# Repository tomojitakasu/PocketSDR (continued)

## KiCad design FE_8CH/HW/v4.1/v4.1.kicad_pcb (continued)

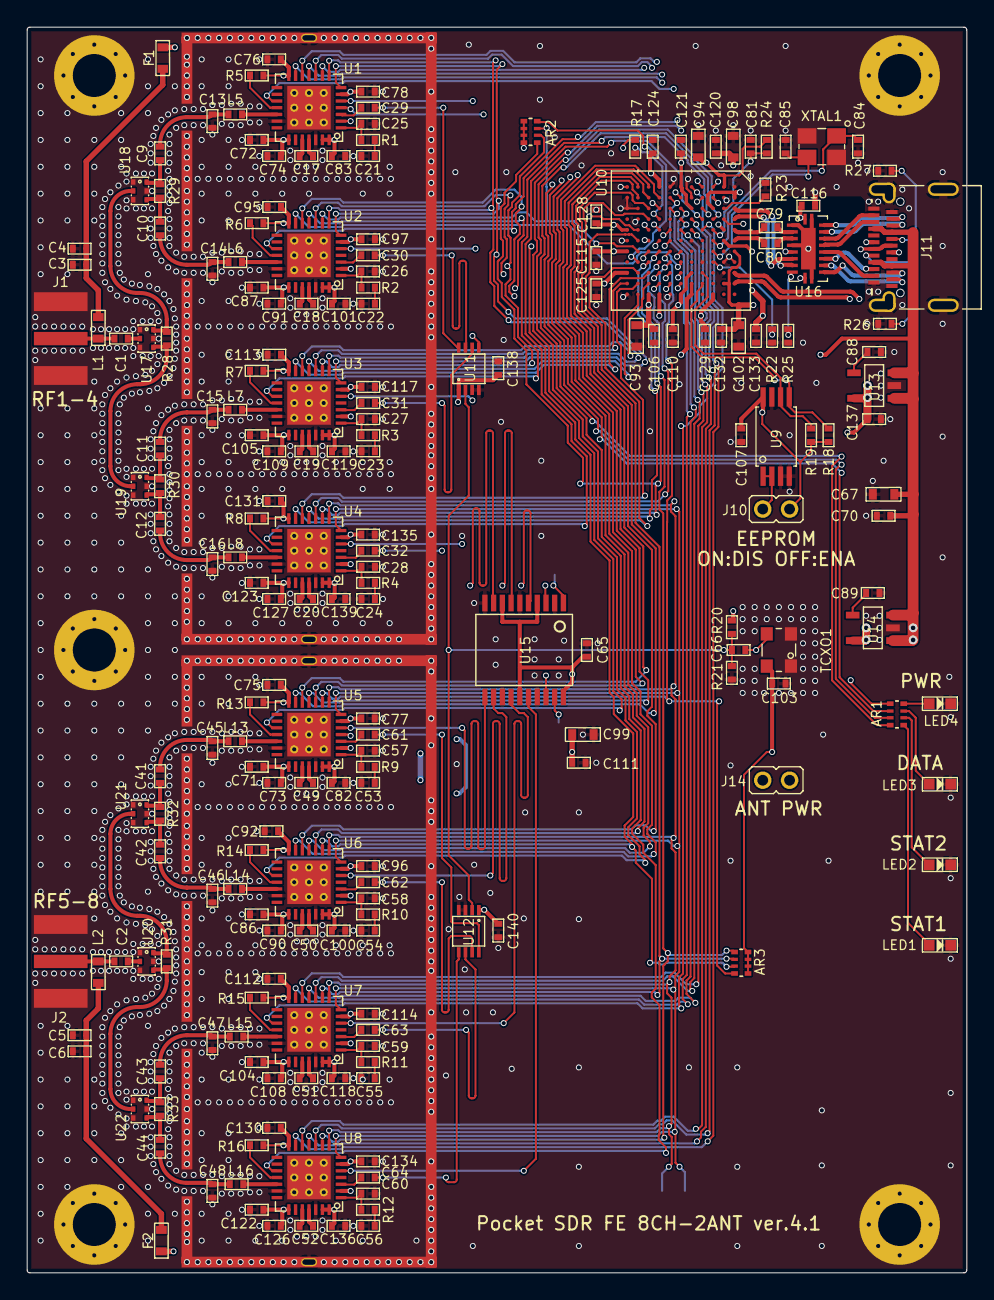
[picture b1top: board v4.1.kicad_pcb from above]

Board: 4 copper layers, 70.0 x 92.8 mm, 221 parts (0 on the bottom side), 195 nets.

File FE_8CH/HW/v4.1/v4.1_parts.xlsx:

No | Reference | Value | Package | Qty | Assy | Supplier | Supplier Part # | Digikey Part # | Price | Total | URL
1 | U1-U8 | RF RX GNSS 1.227/1.575GHZ | TQFN28 | 8 | 8 | Maxim | MAX2771ETI+ | MAX2771ETI+-ND | 1883 | 15064 | https://www.digikey.jp/products/ja?keywords=MAX2771ETI%2B-ND
2 | U9 | I2C EEPROM 1MBIT | 8-TSSOP | 1 | 1 | Microchip | AT24CM01-XHM-T | AT24CM01-XHM-TCT-ND | 284 | 284 | https://www.digikey.jp/ja/products/detail/microchip-technolo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
3 | U10 | EZ-USB FX3 USB 3.0 RAM 512KB | 121-TFBGA | 1 | 1 | Cypress | CYUSB3014-BZXC | 448-CYUSB3014-BZXC-ND | 5308 | 5308 | https://www.digikey.jp/ja/products/detail/infineon-technolog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
4 | U11, U12 | IC CLK BUFFER 1:4 | 8-VSSOP | 2 | 2 | Nexperia | 74AVC9112DCH | 1727-7845-1-ND | 91 | 182 | https://www.digikey.jp/ja/products/detail/nexperia-usa-inc/7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
5 | U13 | LDO 1.2V 500mA | SOT23-5 | 1 | 1 | MaxLinear | SPX3819M5-L-1-2/TR | 1016-1872-1-ND | 88 | 88 | https://www.digikey.jp/ja/products/detail/maxlinear-inc/SPX3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
6 | U14 | LDO 3.3V 500mA | SOT23-5 | 1 | 1 | MaxLinear | SPX3819M5-L-3-3/TR | 1016-1873-1-ND | 88 | 88 | https://www.digikey.jp/ja/products/detail/maxlinear-inc/SPX3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
7 | U15 | IC CLK BUFFER 1:10 100MHZ | 20SSOP | 1 | 1 | Renesas | 74FCT3807APYG | 800-1628-5-ND | 295 | 295 | https://www.digikey.jp/ja/products/detail/renesas-electronic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
8 | U16 | IC MUX/DEMUX USB 3.0 | 20TQFN | 1 | 1 | Diodes | PI3USB302-AZBEX | PI3USB302-AZBEXCT-ND | 419 | 419 | https://www.digikey.jp/ja/products/detail/diodes-incorporate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
9 | U17-U22 | RF PWR DVDR 950MHZ-2.15GHZ | 2.04 x 1.29 SMD | 6 | 6 | TTM | PD0922J5050S2HF | 1173-1094-1-ND | 160 | 960 | https://www.digikey.jp/product-detail/ja/anaren/PD0922J5050S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
10 | TCXO1 | TCXO 24.000 MHz 0.5ppm Clipped-sine | 2.5 x 2 SMD | 1 | 1 | Epson | TG2520SMN 24.0000M-MCGNNM3 | - | 567.6 | 567.6 | https://www.mouser.jp/ProductDetail/Epson-Timing/TG2520SMN-2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
11 | XTAL1 | XTAL 19.2MHz | 2.5 x 2 SMD | 1 | 1 | NDK | CS05400-19.2M | 644-CS05400-19.2MCT-ND | 132 | 132 | https://www.digikey.jp/ja/products/detail/ndk-america-inc/CS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
12 | C3, C5, C71, C72, C86, C87, C104, C105, C122, C123 | 100pF | C1005 | 10 | 10 | Kyocera | KGM05ACG1H101JH | 478-KGM05ACG1H101JHCT-ND | 3.8 | 38 | https://www.digikey.jp/ja/products/detail/kyocera-avx/KGM05A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
13 | C4, C6, C65, C70, C73-C80, C82, C83, C88-C92, C95-C97, C100, C101, C103, C106-C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 | 0.1uF | C1005 | 58 | 58 | Kyocera | KGM05AR71C104KH | 478-KGM05AR71C104KHCT-ND | 2.5 | 145 | https://www.digikey.jp/ja/products/detail/kyocera-avx/KGM05A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
14 | C1, C2, C9-C12, C17-C20, C41-C44, C49-C52 | 470pF | C1005 | 18 | 18 | Kyocera | KGM05AR71H471KH | 478-KGM05AR71H471KHCT-ND | 3 | 54 | https://www.digikey.jp/ja/products/detail/kyocera-avx/KGM05A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
15 | C13-C16, C45-C48 | 1.7pF | C1005 | 8 | 8 | Murata | GJM1555C1H1R7BB01D | 490-6074-1-ND | 8.9 | 71.2 | https://www.digikey.jp/ja/products/detail/murata-electronics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
16 | C21-C24, C53-C56 | 750pF | C1005 | 8 | 8 | Taiyo Yuden | UMK105CH751JVHF | 587-5098-1-ND | 8 | 64 | https://www.digikey.jp/ja/products/detail/taiyo-yuden/UMK105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
17 | C25-C28, C57-C60 | 15pF | C1005 | 8 | 8 | Kyocera | KGM05ACG1H150JH | 478-KGM05ACG1H150JHCT-ND | 3.3 | 26.4 | https://www.digikey.jp/ja/products/detail/kyocera-avx/KGM05A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
18 | C29-C32, C61-C64, C66 | 0.01uF | C1005 | 9 | 9 | Kyocera | KGM05AR71C103KH | 478-KGM05AR71C103KHCT-ND | 2.4 | 21.599999999999998 | https://www.digikey.jp/ja/products/detail/kyocera-avx/KGM05A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
19 | C67, C93, C94, C98, C99, C102 | 22uF | C1608 | 6 | 6 | Murata | GRM188R61A226ME15D | 490-10476-1-ND | 31 | 186 | https://www.digikey.jp/ja/products/detail/murata-electronics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
20 | C81 | 1uF | C1005 | 1 | 1 | Kyocera | KGM05AR51A105KH | 478-KGM05AR51A105KHCT-ND | 10.8 | 10.8 | https://www.digikey.jp/ja/products/detail/kyocera-avx/KGM05A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
21 | C84, C85 | 13pF | C1005 | 2 | 2 | Murata | GJM1555C1H130FB01D | 490-GJM1555C1H130FB01DCT-ND | 13 | 26 | https://www.digikey.jp/ja/products/detail/murata-electronics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
22 | L1, L2 | 68nH | L1608 | 2 | 2 | Murata | LQW18AN68NJ00D | 490-1178-1-ND | 17.399999999999999 | 34.799999999999997 | https://www.digikey.jp/ja/products/detail/murata-electronics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
23 | L5-L8, L13-L16 | 5.6nH | L1005 | 8 | 8 | Murata | LQW15AN5N6C8ZD | 490-15522-1-ND | 16.2 | 129.6 | https://www.digikey.jp/ja/products/detail/murata-electronics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
24 | R1-R4, R9-R12 | 15K | R1005 | 8 | 8 | YAGEO | RC0402JR-0715KL | 311-15KJRCT-ND | 1.7 | 13.6 | https://www.digikey.jp/ja/products/detail/yageo/RC0402JR-071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
25 | R5-R8, R13-R17, R25 | 10K | R1005 | 10 | 10 | YAGEO | RC0402JR-0710KL | 311-10KJRCT-ND | 1.7 | 17 | https://www.digikey.jp/ja/products/detail/yageo/RC0402JR-071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
26 | R18, R19 | 2.2K | R1005 | 2 | 2 | YAGEO | RC0402JR-072K2L | 311-2.2KJRCT-ND | 1.7 | 3.4 | https://www.digikey.jp/ja/products/detail/yageo/RC0402JR-072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
27 | R20, R21, R24 | 100K | R1005 | 3 | 3 | YAGEO | RC0402JR-07100KL | 311-100KJRCT-ND | 1.3 | 3.9000000000000004 | https://www.digikey.jp/ja/products/detail/yageo/RC0402JR-071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
28 | R22 | 6.04K 1% | R1005 | 1 | 1 | YAGEO | RC0402FR-076K04L | YAG2293CT-ND | 1.4 | 1.4 | https://www.digikey.jp/ja/products/detail/yageo/RC0402FR-076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
29 | R23 | 200 1% | R1005 | 1 | 1 | YAGEO | RC0402FR-07200RL | 311-200LRCT-ND | 1.4 | 1.4 | https://www.digikey.jp/ja/products/detail/yageo/RC0402FR-072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
30 | R26,R27 | 5.1K | R1005 | 2 | 2 | YAGEO | RC0402FR-135K1L | 13-RC0402FR-135K1LCT-ND | 1.4 | 2.8 | https://www.digikey.jp/ja/products/detail/yageo/RC0402FR-135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
31 | R28-R33 | 100 | R1005 | 6 | 6 | YAGEO | RC0402JR-07100RL | 311-100JRCT-ND | 2.9 | 17.399999999999999 | https://www.digikey.jp/ja/products/detail/yageo/RC0402JR-071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
32 | AR1 | 1K x 4 | ARRAY_REG__EXB28V | 1 | 1 | Panasonic | EXB-28V102JX | Y7102CT-ND | 8.1999999999999993 | 8.1999999999999993 | https://www.digikey.jp/products/ja?keywords=Y7102CT-ND
33 | AR2, AR3 | 10K x 4 | ARRAY_REG__EXB28V | 2 | 2 | Panasonic | EXB-28V103JX | Y7103CT-ND | 8.1999999999999993 | 16.399999999999999 | https://www.digikey.jp/ja/products/detail/panasonic-electron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
34 | LED1-LED4 | LED white | LED1608 | 4 | 4 | QT Brightek | QBLP601-IW | 1516-1057-1-ND | 32.1 | 128.4 | https://www.digikey.jp/ja/products/detail/qt-brightek-qtb/QB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
35 | F1, F2 | PolySwitch 12V, 8 Ohm, Trip 250 mA | POLYSW1608 | 2 | 2 | Littelfuse Inc | FEMTOSMDC010F-2 | FEMTOSMDC010F-2 | 86 | 172 | https://www.digikey.jp/ja/products/detail/littelfuse-inc/FEM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
36 | J1, J2 | SMA JACK EDGE MNT | SMA-F-EDGE, 6.4x6.4x14.0 | 2 | 0 | uxcell | - | - | 157.6 | 315.2 | https://www.amazon.co.jp/uxcell-a11053100ux0317-RF%E3%82%B3%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
37 | J10, J14 | PINH_2MM_2P | PINH_2MM_2P | 2 | 0 | Harwin | M22-2510205 | 952-1311-ND | 33 | 66 | https://www.digikey.jp/ja/products/detail/harwin-inc/M22-251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
38 | J10-S,J14-S | CONN SHUNT 2MM | CONN SHUNT 2MM | 2 | 0 | Sullins Connector | SPN02SYBN-RC | S3404-ND | 19 | 38 | https://www.digikey.jp/ja/products/detail/sullins-connector-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
39 | J11 | USB Type-C Receptacle USB 3.2 24p | USB Type-C Receptacle | 1 | 1 | GCT | USB4080-03-A | 2073-USB4080-03-ACT-ND | 226 | 226 | https://www.digikey.jp/ja/products/detail/gct/USB4080-03-A/14659819
40 | J12, J13 | 2-PIECE SHIELD Frame | 44.8x18.2x3.0 | 2 | 0 | Masach | MS448-10F | 2333-MS448-10F-ND | 234 | 468 | https://www.digikey.jp/ja/products/detail/masach-tech-ltd/MS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
41 | J12-S, J13-S | 2-PIECE SHIELD Cover | 44.8x18.2x3.0 | 2 | 0 | Masach | MS448-10C | 2333-MS448-10C-ND | 230 | 460 | https://www.digikey.jp/ja/products/detail/masach-tech-ltd/MS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
42
 | Subtotal |  |  | 215 | 205 |  |  |  |  | 26154.100000000006
43 | PCB | FR-4, 4-layer | 70 x 92.8 x 1.6 mm | 1 | 0 | JLCPCB |  |  | 784.5 | 784.5 | 5pcs + metal mask
44 | CASE BODY-T | SLA(Resin), Black, Sanding-General | 97 x 74 x 7.5 mm | 1 | 0 | JLC3DP |  |  | 777 | 777 | 2pcs (T+B)
45 | CASE BODY-B | SLA(Resin), Black, Sanding-General | 97 x 74 x 7.5 mm | 1 | 0 | JLC3DP |  |  | 0 | 0
 | Subtotal |  |  |  |  |  |  |  |  | 1561.5
 | Total |  |  |  |  |  |  |  |  | 27715.600000000006

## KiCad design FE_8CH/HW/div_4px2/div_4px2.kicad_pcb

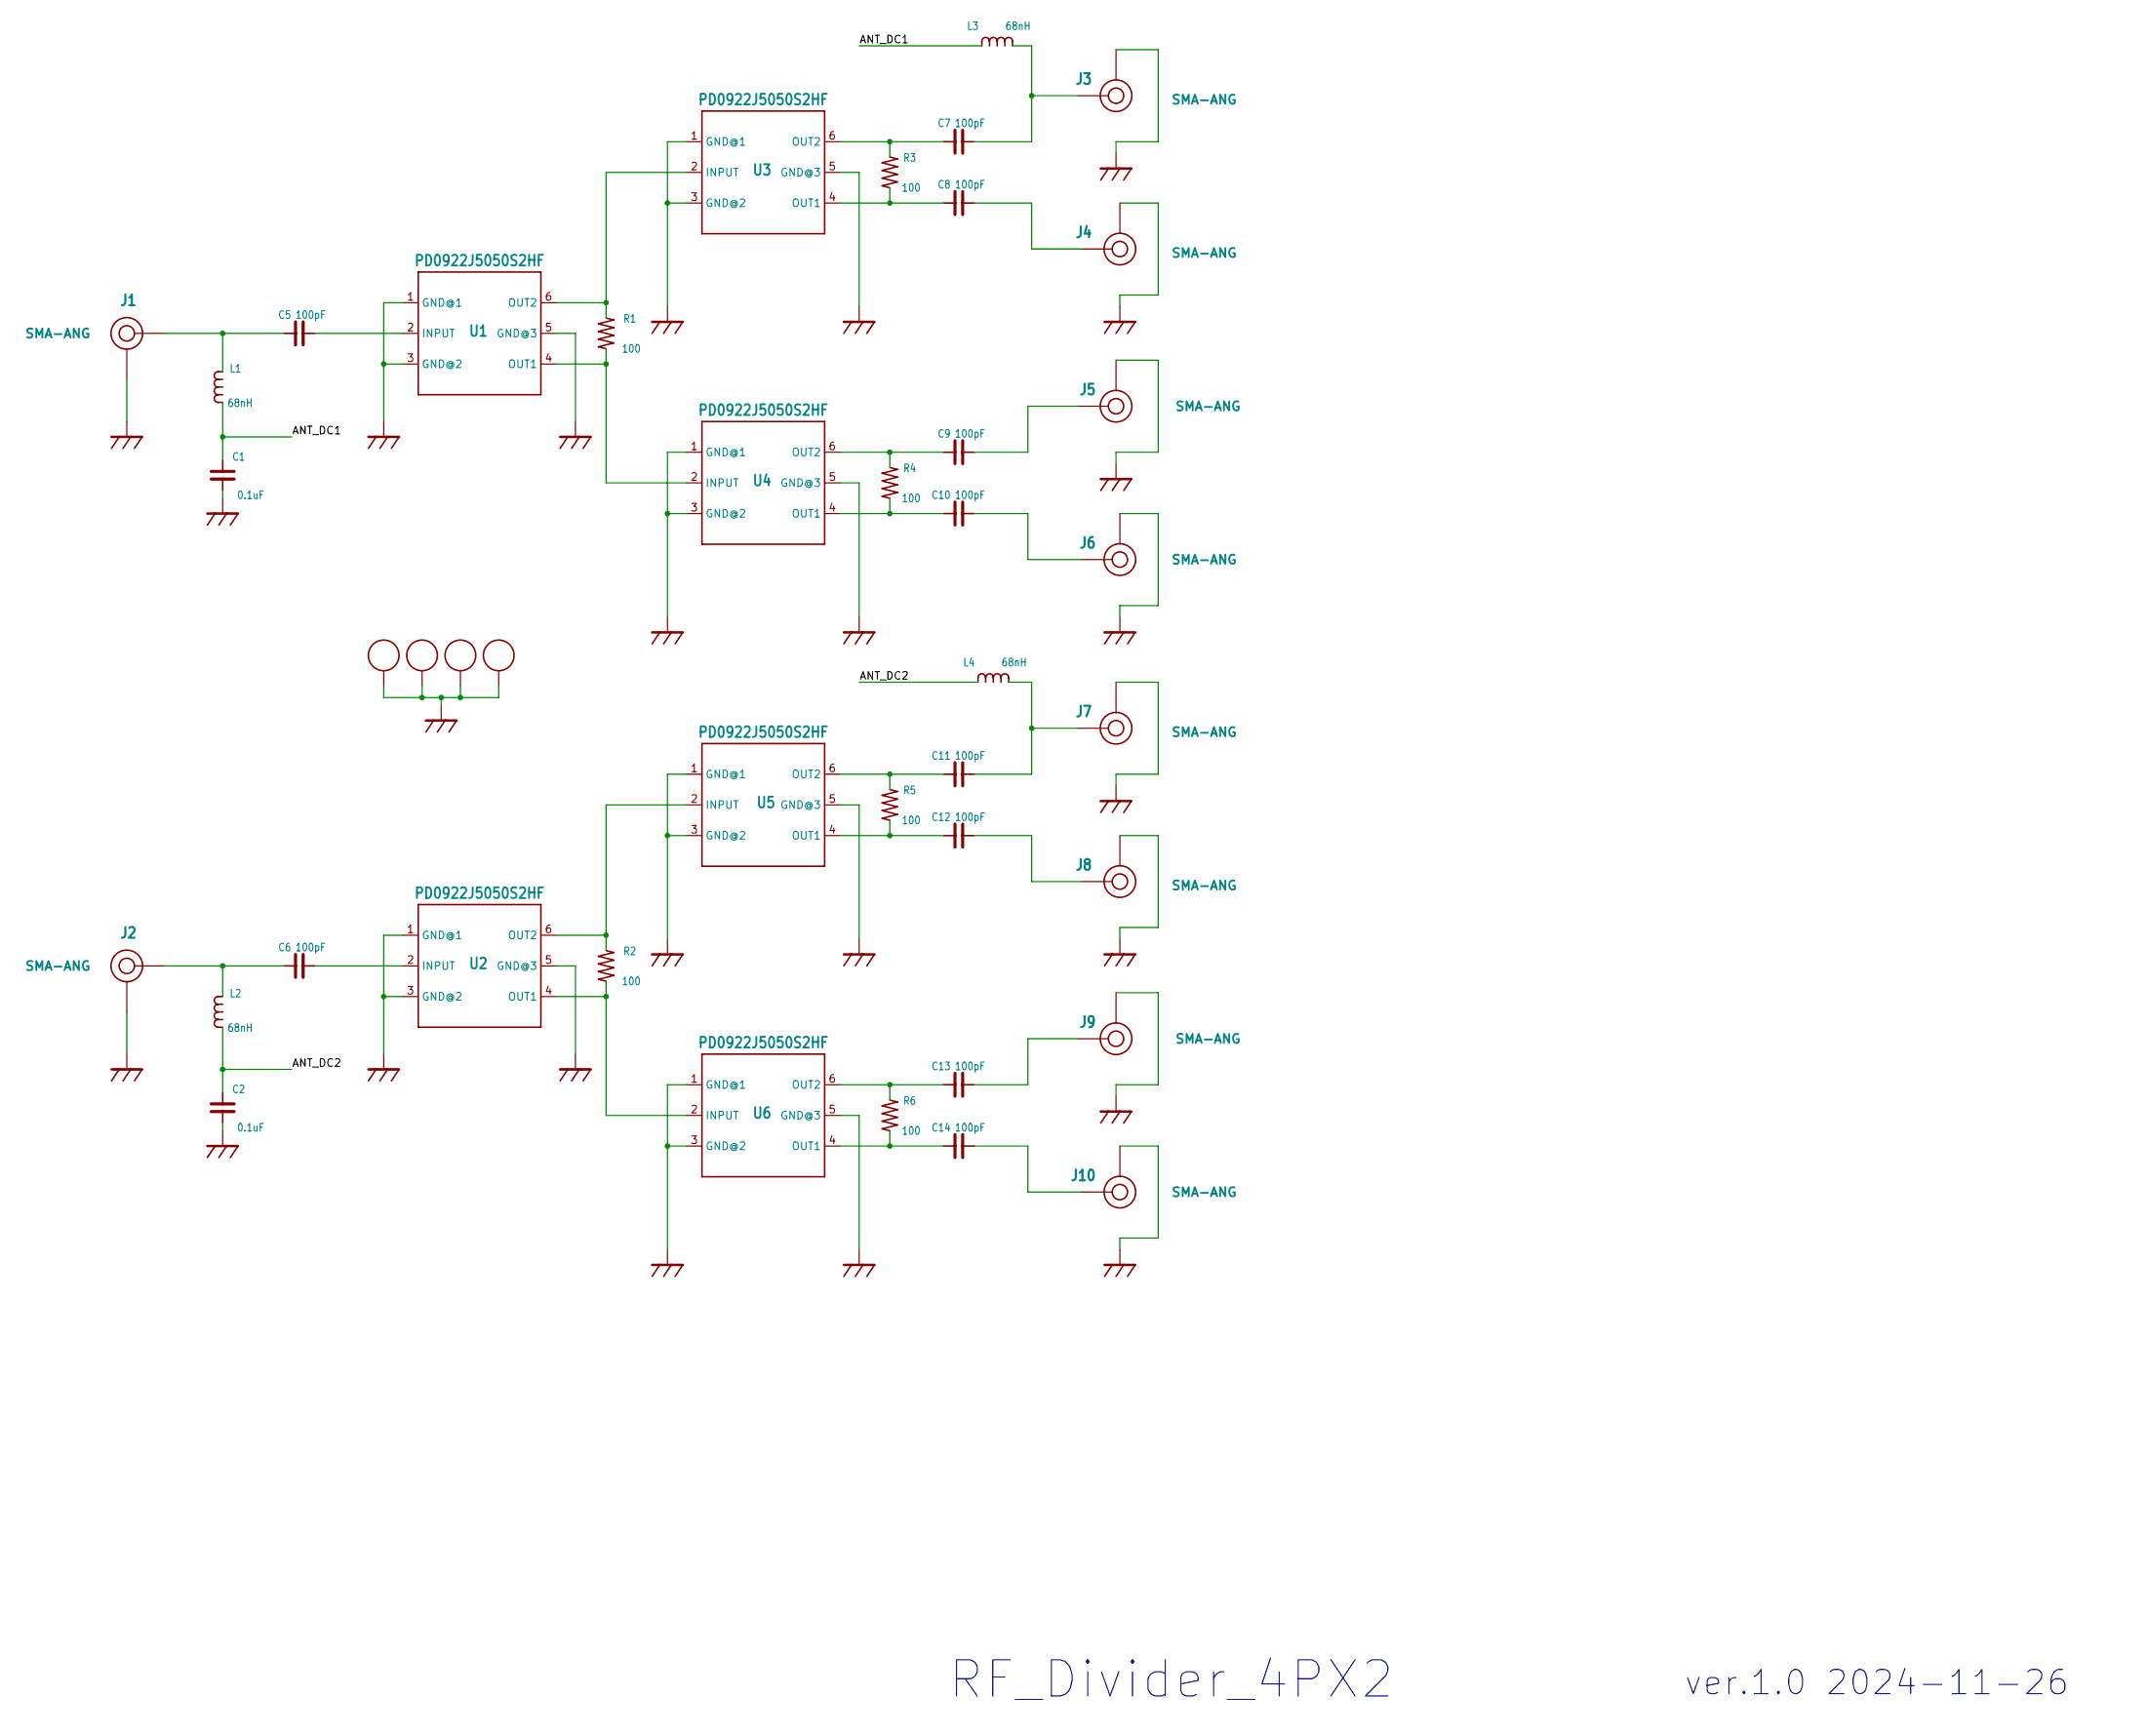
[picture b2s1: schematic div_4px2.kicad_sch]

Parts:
C1, C2: 0.1uF; C1005
C5, C6, C7, C8, C9, C10, C11, C12, C13, C14: 100pF; C1005
J1, J2, J3, J4, J5, J6, J7, J8, J9, J10: SMA-ANG
L1, L2, L3, L4: 68nH; C1608
PAD1, PAD2, PAD3, PAD4: CPAD_3.2MM
R1, R2, R3, R4, R5, R6: 100; C1005
U1, U2, U3, U4, U5, U6: PD0922J5050S2HF; RF_DIV

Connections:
/ANT_DC1: C1.2, L1.1, L3.1
/ANT_DC2: C2.2, L2.1, L4.1
GND: C1.1, C2.1, J1.P2 (GND), J1.P3 (GND), J1.P4 (GND), J1.P5 (GND), J2.P2 (GND), J2.P3 (GND), J2.P4 (GND), J2.P5 (GND), J3.P2 (GND), J3.P3 (GND), J3.P4 (GND), J3.P5 (GND), J4.P2 (GND), J4.P3 (GND), J4.P4 (GND), J4.P5 (GND), J5.P2 (GND), J5.P3 (GND), J5.P4 (GND), J5.P5 (GND), J6.P2 (GND), J6.P3 (GND), J6.P4 (GND), J6.P5 (GND), J7.P2 (GND), J7.P3 (GND), J7.P4 (GND), J7.P5 (GND), J8.P2 (GND), J8.P3 (GND), J8.P4 (GND), J8.P5 (GND), J9.P2 (GND), J9.P3 (GND), J9.P4 (GND), J9.P5 (GND), J10.P2 (GND), J10.P3 (GND), J10.P4 (GND), J10.P5 (GND), PAD1.EP, PAD2.EP, PAD3.EP, PAD4.EP, U1.1 (GND@1), U1.3 (GND@2), U1.5 (GND@3), U2.1 (GND@1), U2.3 (GND@2), U2.5 (GND@3), U3.1 (GND@1), U3.3 (GND@2), U3.5 (GND@3), U4.1 (GND@1), U4.3 (GND@2), U4.5 (GND@3), U5.1 (GND@1), U5.3 (GND@2), U5.5 (GND@3), U6.1 (GND@1), U6.3 (GND@2), U6.5 (GND@3)
unnamed: C5.1, J1.P1 (RF), L1.2
unnamed: C6.1, J2.P1 (RF), L2.2
unnamed: C7.2, J3.P1 (RF), L3.2
unnamed: C8.2, J4.P1 (RF)
unnamed: C9.2, J5.P1 (RF)
unnamed: C10.2, J6.P1 (RF)
unnamed: C11.2, J7.P1 (RF), L4.2
unnamed: C12.2, J8.P1 (RF)
unnamed: C13.2, J9.P1 (RF)
unnamed: C14.2, J10.P1 (RF)
unnamed: R1.1, U1.4 (OUT1), U4.2 (INPUT)
unnamed: R1.2, U1.6 (OUT2), U3.2 (INPUT)
unnamed: R2.1, U2.4 (OUT1), U6.2 (INPUT)
unnamed: R2.2, U2.6 (OUT2), U5.2 (INPUT)
unnamed: C8.1, R3.1, U3.4 (OUT1)
unnamed: C7.1, R3.2, U3.6 (OUT2)
unnamed: C10.1, R4.1, U4.4 (OUT1)
unnamed: C9.1, R4.2, U4.6 (OUT2)
unnamed: C12.1, R5.1, U5.4 (OUT1)
unnamed: C11.1, R5.2, U5.6 (OUT2)
unnamed: C14.1, R6.1, U6.4 (OUT1)
unnamed: C13.1, R6.2, U6.6 (OUT2)
unnamed: C5.2, U1.2 (INPUT)
unnamed: C6.2, U2.2 (INPUT)

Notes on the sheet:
RF_Divider_4PX2
ver.1.0 2024-11-26

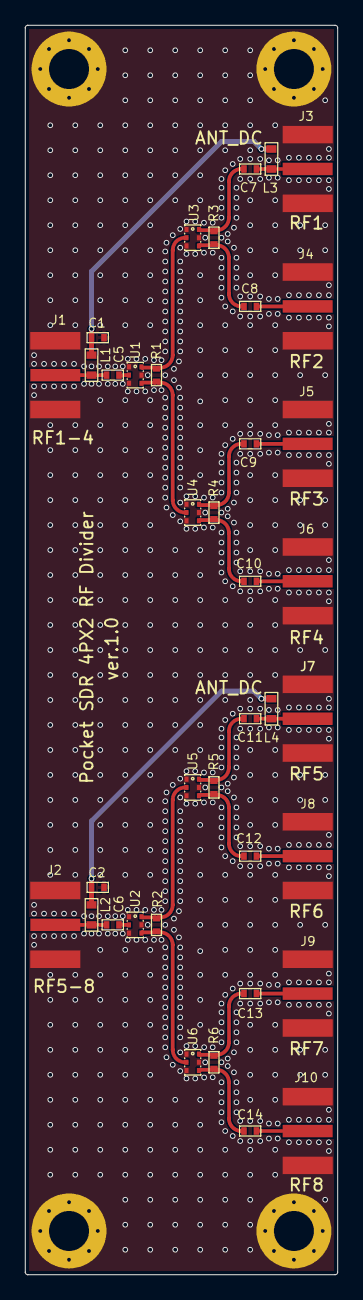
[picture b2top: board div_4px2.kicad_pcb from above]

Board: 4 copper layers, 25.0 x 100.0 mm, 42 parts (0 on the bottom side), 27 nets.

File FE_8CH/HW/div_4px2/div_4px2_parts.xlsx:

No | Ref | Value | Package | Qnty | Assy | Supplier | Supplier Part # | Digikey Part # | Price | Total | URL
1 | U1,U2,U3,U4,U5,U6 | RF PWR DVDR 950MHZ-2.15GHZ | 2.04 x 1.29 SMD | 6 | 6 | TTM | PD0922J5050S2HF | 1173-1094-1-ND | 160 | 960 | https://www.digikey.jp/product-detail/ja/anaren/PD0922J5050S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
2 | C1,C2 | 0.1uF | C1005 | 2 | 2 | 39 | Kyocera | KGM05AR71C104KH | 478-KGM05AR71C104KHCT-ND | 2.2000000000000002 | 4.4000000000000004 | https://www.digikey.jp/ja/products/detail/kyocera-avx/KGM05A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
3 | C5,C6,C7,C8,C9,C10,C11,C12,C13,C14 | 100pF | C1005 | 10 | 10 | Kyocera | KGM05ACG1H101JH | 478-KGM05ACG1H101JHCT-ND | 3.7 | 37 | https://www.digikey.jp/ja/products/detail/kyocera-avx/KGM05A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
4 | L1,L2,L3,L4 | 68nH | L1608 | 4 | 4 | Murata | LQW18AN68NJ00D | 490-1178-1-ND | 24 | 96 | https://www.digikey.jp/ja/products/detail/murata-electronics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
5 | R1,R2,R3,R4,R5,R6 | 100 | R1005 | 6 | 6 | YAGEO | RC0402JR-07100RL | 311-100JRCT-ND | 2.9 | 17.399999999999999 | https://www.digikey.jp/ja/products/detail/yageo/RC0402JR-071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
6 | J1,J2,J3,J4,J5,J6,J7,J8,J9,J10 | SMA JACK EDGE MNT | SMA-ANG | 10 | 0 | uxcell | - | - | 157.6 | 1576 | https://www.amazon.co.jp/uxcell-a11053100ux0317-RF%E3%82%B3%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
 | Subtotal |  |  |  | 28 |  |  |  |  | 2688.6000000000004
 | PCB | FR4, 4-layer | 72 x 26 x 1.6 mm | 1 | 0 | JLCPCB |  |  | 701.1 | 701.1 | https://jlcpcb.com/ | 5pcs
 | CASE | SLA(Resin), Snading-General | 104 x 29 x 12 mm | 1 | 0 | JLC3DP |  |  | 714 | 714
 | Subtotal |  |  |  |  |  |  |  |  | 1415.1
 | Total |  |  |  |  |  |  |  |  | 4103.7000000000007
